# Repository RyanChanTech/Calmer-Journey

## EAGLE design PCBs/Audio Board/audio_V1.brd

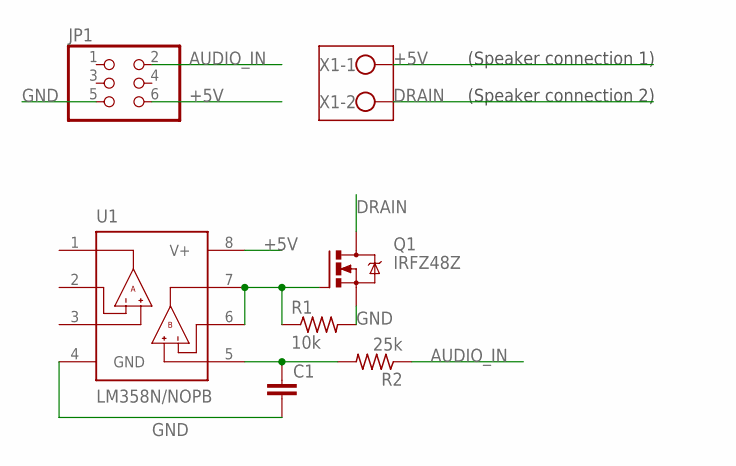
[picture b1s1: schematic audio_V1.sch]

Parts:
C1: C-EU025-025X050; C025-025X050
JP1: PINHD-2X3; 2X03
Q1: IRFZ48Z; TO220BH
R1: 10k; 0204/7
R2: 25k; 0204/7
U1: LM358N/NOPB; DIP794W45P254L959H508Q8
X1: W237-102

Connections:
+5V: JP1.6, U1.8 (V+), X1.1
AUDIO_IN: JP1.2, R2.1
DRAIN: Q1.D, X1.2
GND: C1.2, JP1.5, Q1.S, R1.2, U1.4 (GND)
unnamed: C1.1, R2.2, U1.5 (+INB)
unnamed: Q1.G, R1.1, U1.6 (-INB), U1.7 (OUTB)

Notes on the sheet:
(Speaker connection 1)
(Speaker connection 2)

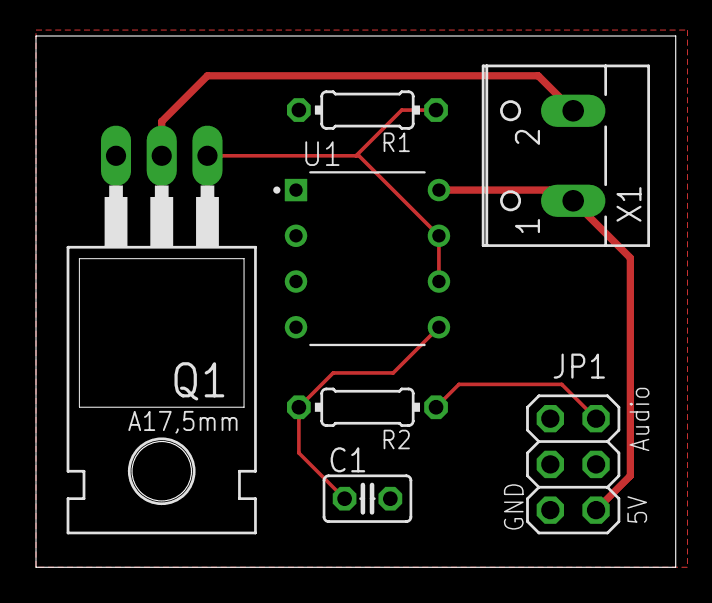
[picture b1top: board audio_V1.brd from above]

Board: 2 copper layers, 35.5 x 29.5 mm, 7 parts (0 on the bottom side), 6 nets.

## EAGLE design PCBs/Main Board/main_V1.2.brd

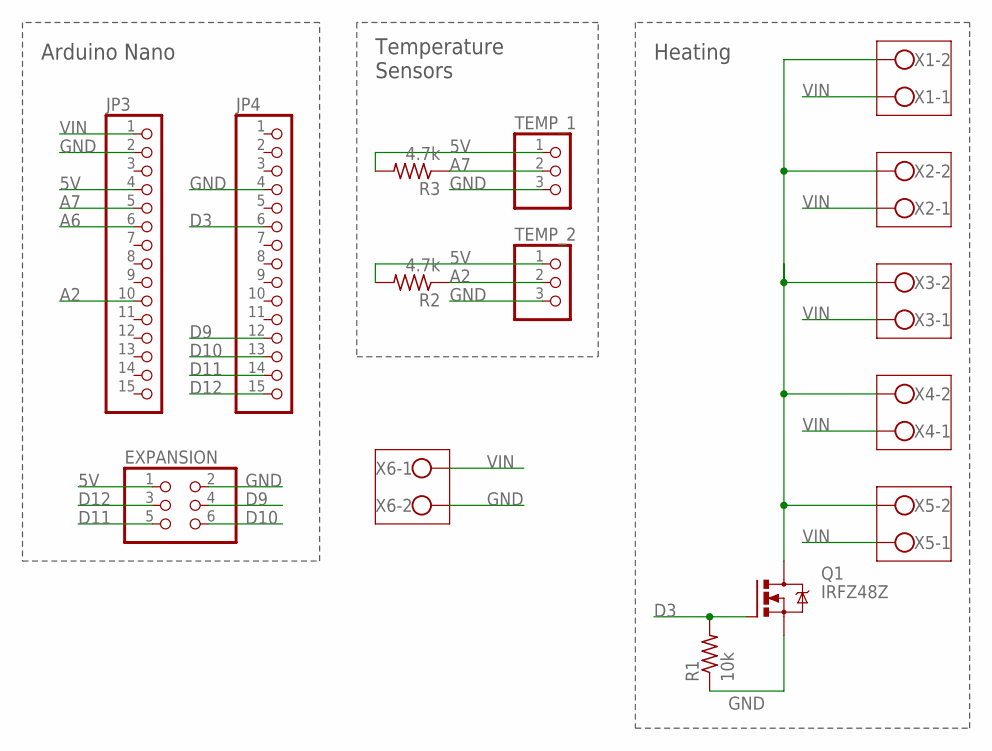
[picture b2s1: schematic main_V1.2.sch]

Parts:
EXPANSION: PINHD-2X3; 2X03
JP3, JP4: PINHD-1X15-CB; 1X15-CB
Q1: IRFZ48Z; TO220BH
R1: 10k; 0204/7
R2, R3: 4.7k; 0204/7
TEMP_1, TEMP_2: PINHD-1X3; 1X03
X1, X2, X3, X4, X5, X6: W237-102

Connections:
5V: EXPANSION.1, JP3.4, R2.2, R3.2, TEMP_1.1, TEMP_2.1
A2: JP3.10, R2.1, TEMP_2.2
A6: JP3.6
A7: JP3.5, R3.1, TEMP_1.2
D3: JP4.6, Q1.G, R1.2
D9: EXPANSION.4, JP4.12
D10: EXPANSION.6, JP4.13
D11: EXPANSION.5, JP4.14
D12: EXPANSION.3, JP4.15
GND: EXPANSION.2, JP3.2, JP4.4, Q1.S, R1.1, TEMP_1.3, TEMP_2.3, X6.2
unnamed: Q1.D, X1.2, X2.2, X3.2, X4.2, X5.2
VIN: JP3.1, X1.1, X2.1, X3.1, X4.1, X5.1, X6.1

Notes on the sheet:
Arduino Nano
Temperature Sensors
Heating

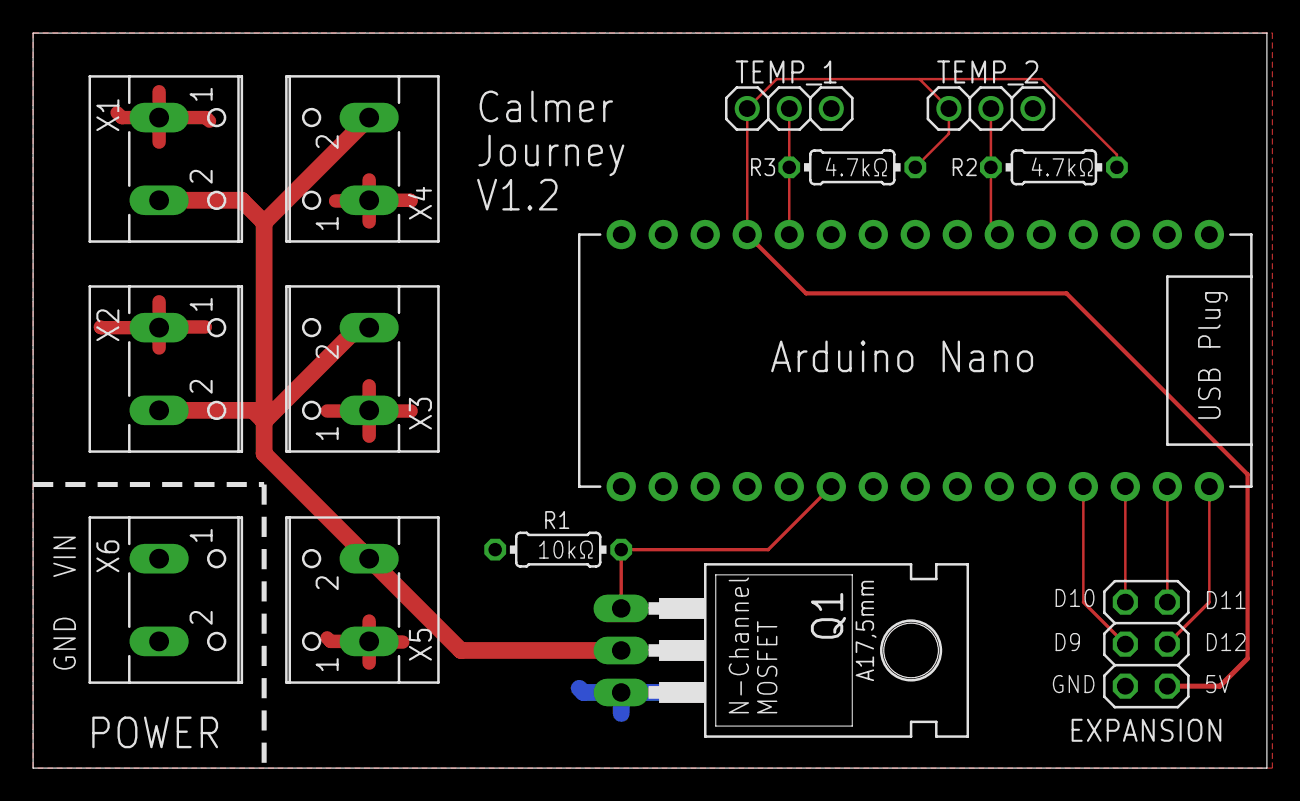
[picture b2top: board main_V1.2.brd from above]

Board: 2 copper layers, 74.6 x 44.4 mm, 15 parts (0 on the bottom side), 11 nets.

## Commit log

2021-11-05 Rename calmer_code_1.ino to calmer_code.ino
2021-11-06 pcb uploads
